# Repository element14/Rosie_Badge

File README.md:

# Rosie_Badge
A soldering project based on the iconic "Rosie" that blinks an LED using a 555 timer

Download and open E_Grrrl.pro with KiCad to see files

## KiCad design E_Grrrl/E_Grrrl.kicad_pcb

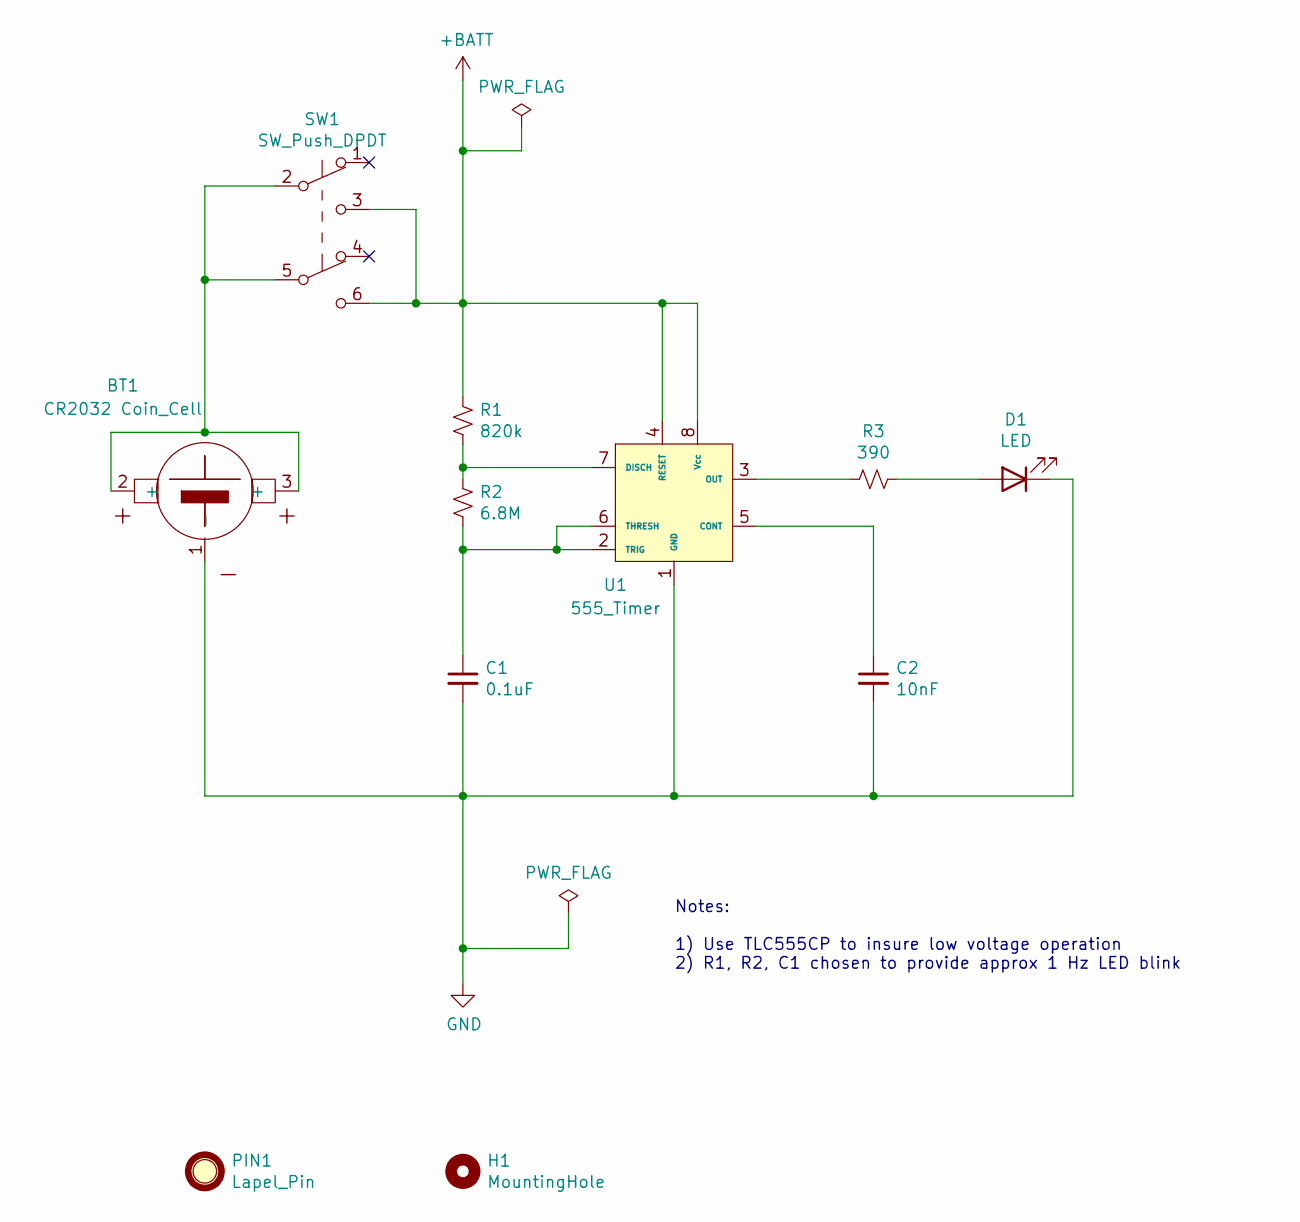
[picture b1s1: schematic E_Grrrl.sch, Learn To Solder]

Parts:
BT1: CR2032 Coin_Cell; Keystone_3002_1x2032
C1: 0.1uF; C_Disc_D3.0mm_W2.0mm_P2.50mm
C2: 10nF; C_Disc_D3.0mm_W2.0mm_P2.50mm
D1: LED; LED_D3.0mm_Horizontal_O1.27mm_Z10.0mm
H1: MountingHole; MountingHole_3.2mm_M3
PIN1: Lapel_Pin
R1: 820k; R_Axial_DIN0207_L6.3mm_D2.5mm_P10.16mm_Horizontal
R2: 6.8M; R_Axial_DIN0207_L6.3mm_D2.5mm_P10.16mm_Horizontal
R3: 390; R_Axial_DIN0207_L6.3mm_D2.5mm_P10.16mm_Horizontal
SW1: SW_Push_DPDT; SW_CK_JS202011AQN_DPDT
U1: 555_Timer; DIP-8_W7.62mm_LongPads

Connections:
+BATT: R1.1, SW1.3 (C), SW1.6 (C), U1.4 (RESET), U1.8 (Vcc)
GND: BT1.1 (-), C1.2, C2.2, D1.1 (K), U1.1 (GND)
unnamed: BT1.2 (+), BT1.3 (+), SW1.2 (B), SW1.5 (B)
unnamed: C1.1, R2.2, U1.2 (TRIG), U1.6 (THRESH)
unnamed: C2.1, U1.5 (CONT)
unnamed: D1.2 (A), R3.1
unnamed: R1.2, R2.1, U1.7 (DISCH)
unnamed: R3.2, U1.3 (OUT)

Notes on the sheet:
Notes: 1) Use TLC555CP to insure low voltage operation 2) R1, R2, C1 chosen to provide approx 1 Hz LED blink

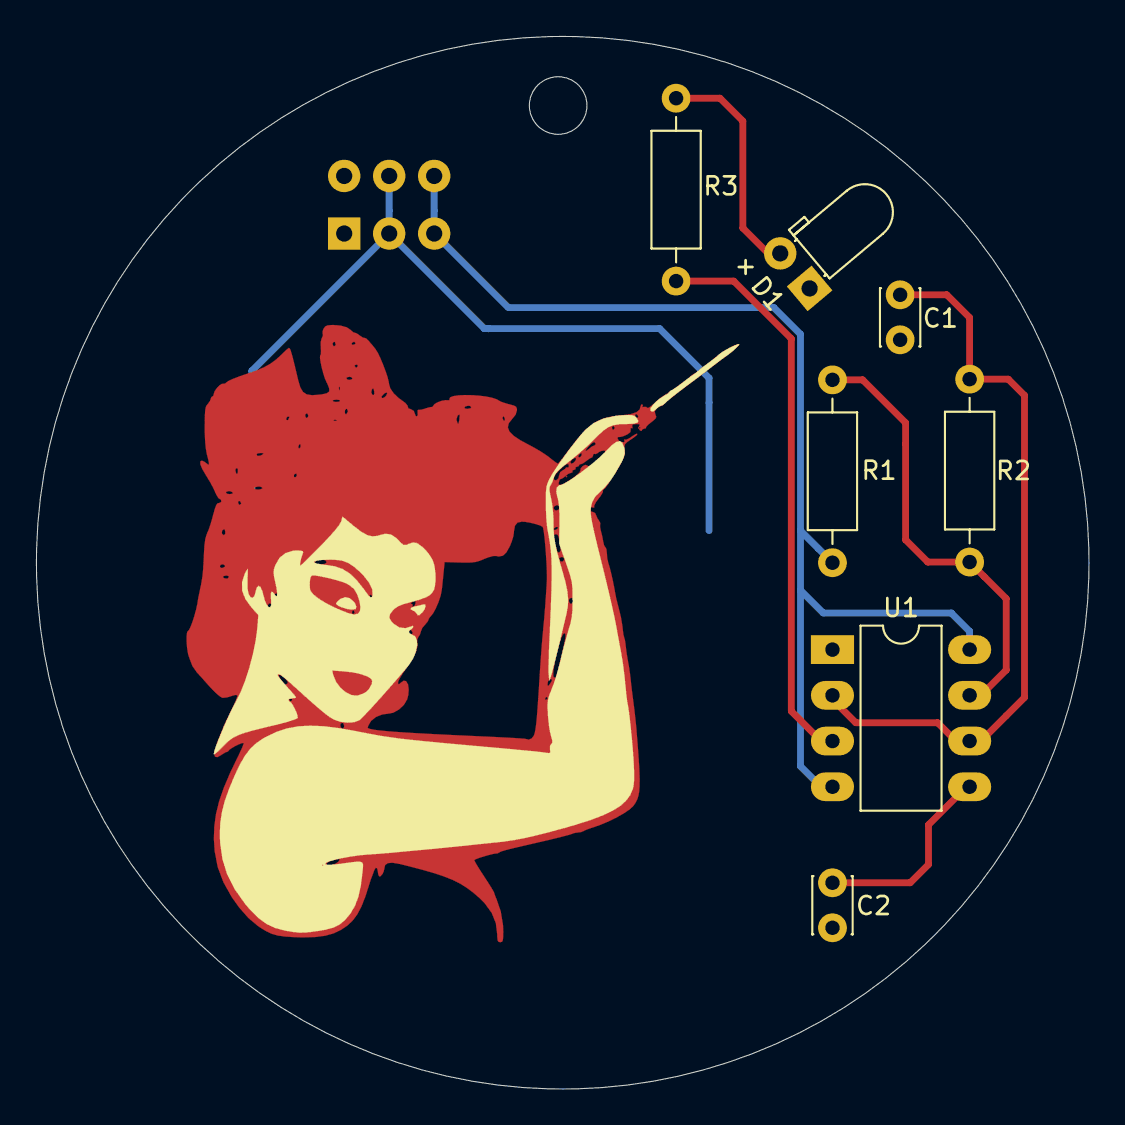
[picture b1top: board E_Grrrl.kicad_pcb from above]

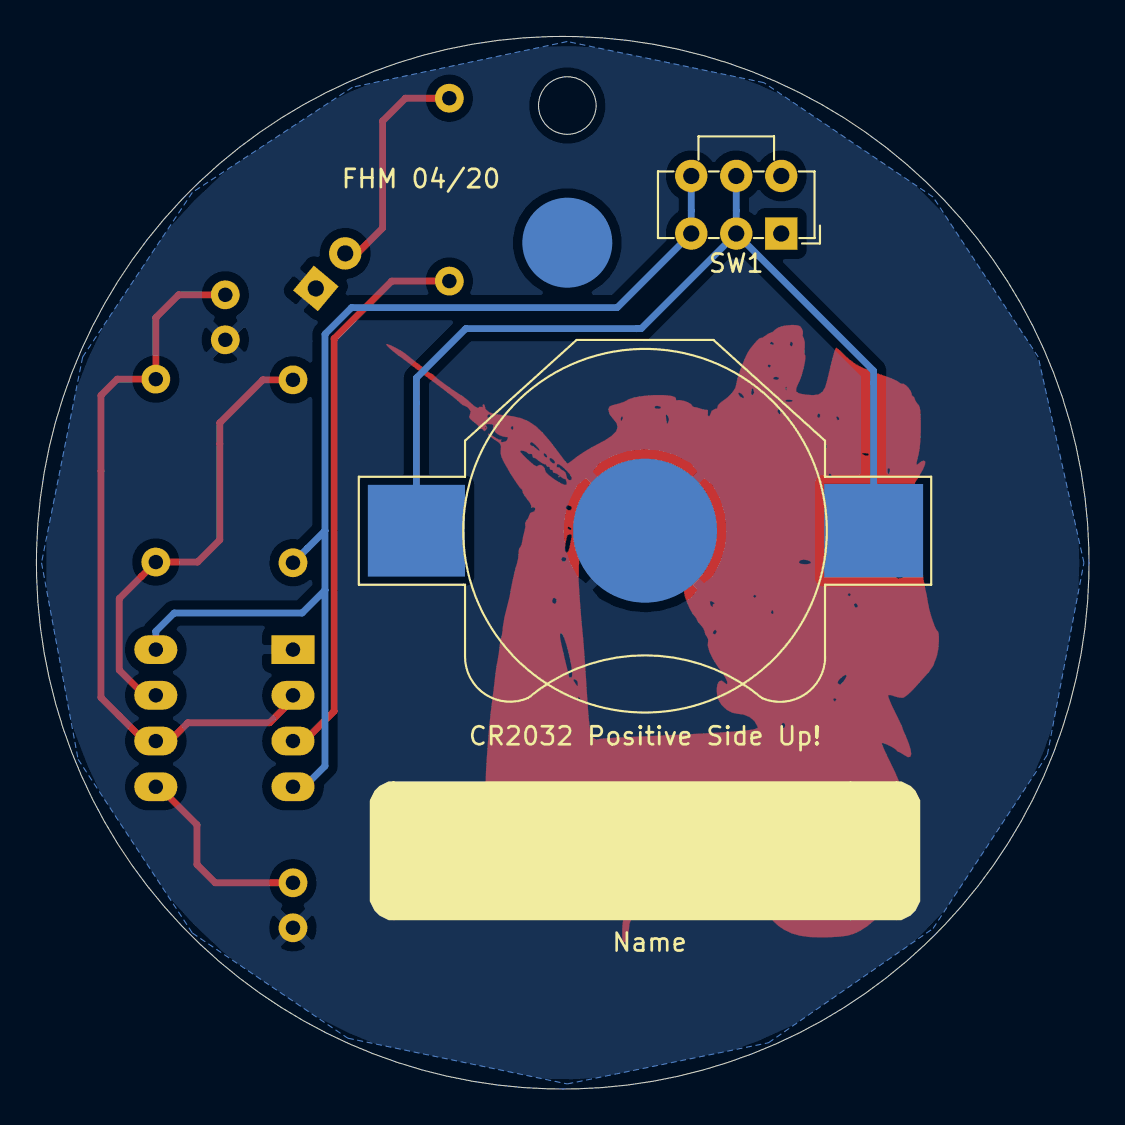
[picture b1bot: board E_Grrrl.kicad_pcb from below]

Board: 2 copper layers, 58.5 x 58.5 mm, 11 parts (3 on the bottom side), 8 nets.
